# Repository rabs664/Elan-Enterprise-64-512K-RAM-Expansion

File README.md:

# Elan-Enterprise-64-512K-RAM-Expansion

>[!CAUTION]
>USE AT YOUR OWN RISK.
>There is always the risk that this 512k RAM Expansion could cause harm to your Enterprise. Although I have tested the 512K RAM Expansion, there is no guarantee that it will work properly under all circumstances.
>
>I am not an Enterprise Expert and still learning about this machine. What you see here is an intepretation of what I have found on the web, see the acknowledgements.

>[!WARNING]
>There is not a lot of room under the keyboard and the jumper wire connectors are a tight fit. There is probably a better solution to this.
>
> Also the EXP1 connector does not have standard spacing and you have to use two separate headers.
>
> 

## Project History
### 27 June 2026
First Releae

## Acknowledgements
- [Supid Humans Inc EP RAM](https://github.com/StupidHumansInc/EP_RAM)
- [Andra Santos](https://github.com/andrastantos/enterprise_mem_extender)

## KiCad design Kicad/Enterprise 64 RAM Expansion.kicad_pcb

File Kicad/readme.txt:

This folder contains the Kicad project files and gerbers.

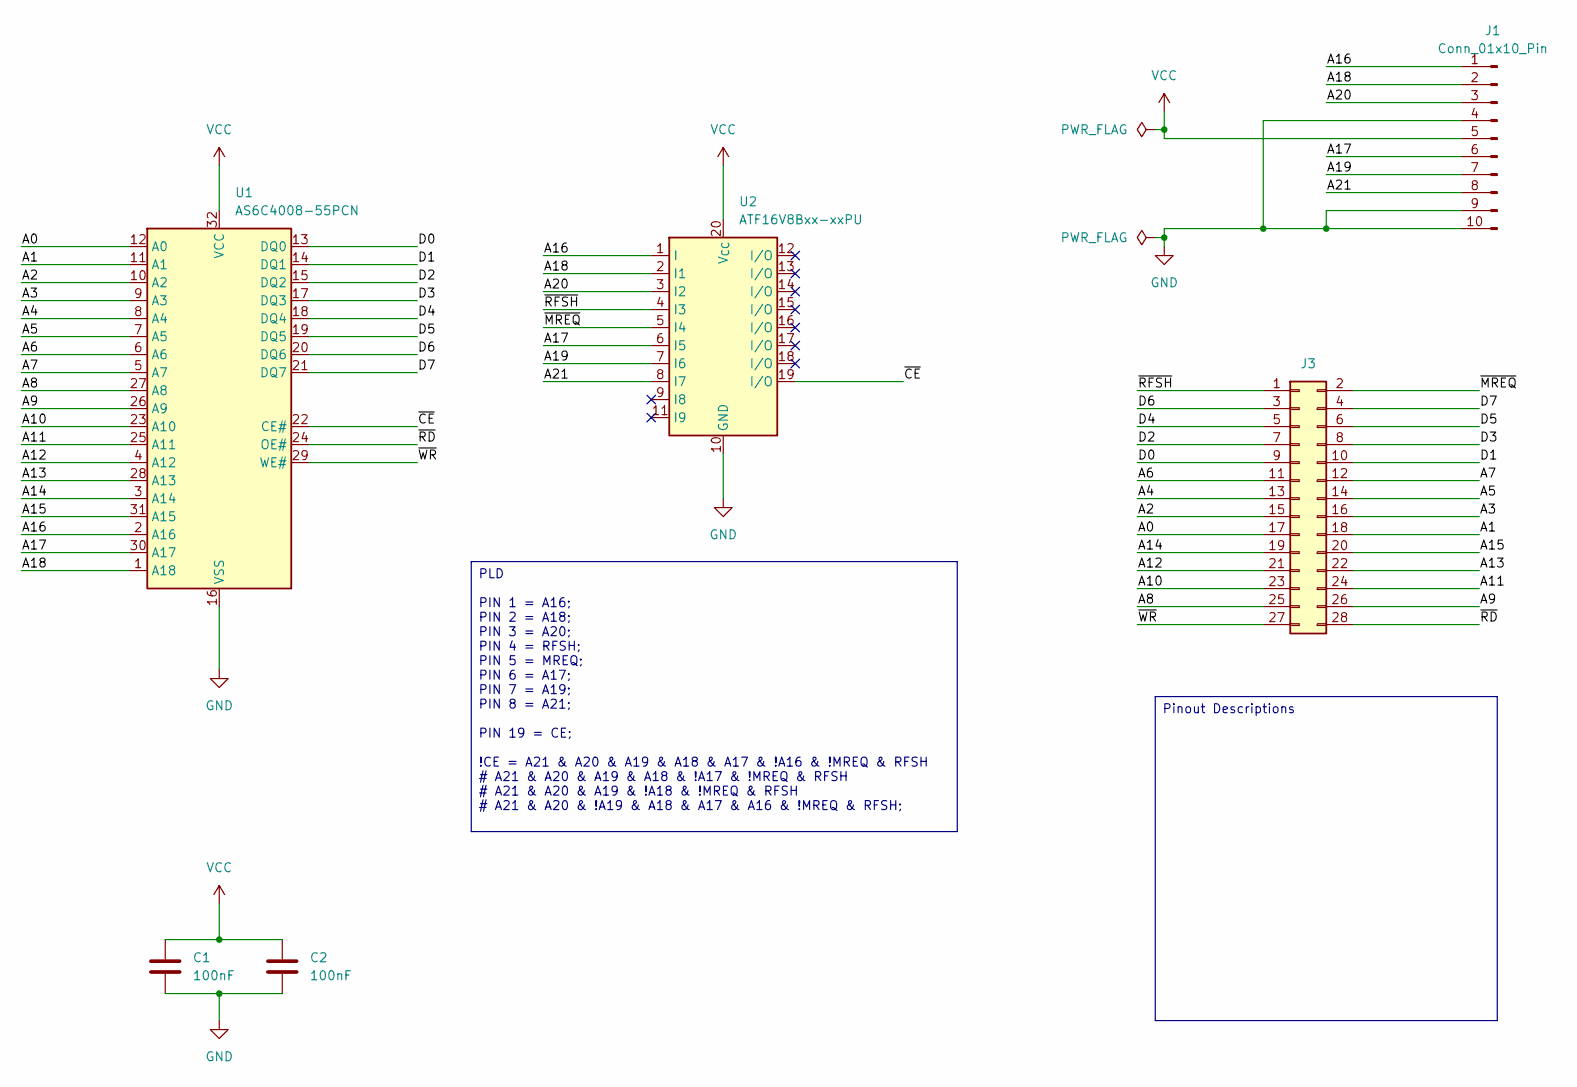
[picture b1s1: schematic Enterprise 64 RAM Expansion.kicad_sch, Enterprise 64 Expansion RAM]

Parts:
C1, C2: 100nF; C_0805_2012Metric_Pad1.18x1.45mm_HandSolder
J1: Conn_01x10_Pin; PinHeader_1x10_P2.54mm_Horizontal
J3: Conn_02x16_Row_Letter_First; PinSocket_2x14_P2.54mm_Vertical
U1: AS6C4008-55PCN; SOP-32_11.305x20.495mm_P1.27mm
U2: ATF16V8Bxx-xxPU; SOIC-20W_7.5x12.8mm_P1.27mm

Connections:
/A0: J3.17, U1.12 (A0)
/A1: J3.18, U1.11 (A1)
/A2: J3.15, U1.10 (A2)
/A3: J3.16, U1.9 (A3)
/A4: J3.13, U1.8 (A4)
/A5: J3.14, U1.7 (A5)
/A6: J3.11, U1.6 (A6)
/A7: J3.12, U1.5 (A7)
/A8: J3.25, U1.27 (A8)
/A9: J3.26, U1.26 (A9)
/A10: J3.23, U1.23 (A10)
/A11: J3.24, U1.25 (A11)
/A12: J3.21, U1.4 (A12)
/A13: J3.22, U1.28 (A13)
/A14: J3.19, U1.3 (A14)
/A15: J3.20, U1.31 (A15)
/A16: J1.1, U1.2 (A16), U2.1 (I)
/A17: J1.6, U1.30 (A17), U2.6 (I5)
/A18: J1.2, U1.1 (A18), U2.2 (I1)
/A19: J1.7, U2.7 (I6)
/A20: J1.3, U2.3 (I2)
/A21: J1.8, U2.8 (I7)
/D0: J3.9, U1.13 (DQ0)
/D1: J3.10, U1.14 (DQ1)
/D2: J3.7, U1.15 (DQ2)
/D3: J3.8, U1.17 (DQ3)
/D4: J3.5, U1.18 (DQ4)
/D5: J3.6, U1.19 (DQ5)
/D6: J3.3, U1.20 (DQ6)
/D7: J3.4, U1.21 (DQ7)
/~CE: U1.22 (CE#), U2.19 (I/O)
/~MREQ: J3.2, U2.5 (I4)
/~RD: J3.28, U1.24 (OE#)
/~RFSH: J3.1, U2.4 (I3)
/~WR: J3.27, U1.29 (WE#)
GND: C1.2, C2.2, J1.4, J1.9, J1.10, U1.16 (VSS), U2.10 (GND)
VCC: C1.1, C2.1, J1.5, U1.32 (VCC), U2.20 (V_{CC})

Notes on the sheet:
Pinout Descriptions
PLD PIN 1 = A16; PIN 2 = A18; PIN 3 = A20; PIN 4 = RFSH; PIN 5 = MREQ; PIN 6 = A17; PIN 7 = A19; PIN 8 = A21; PIN 19 = CE; !CE = A21 & A20 & A19 & A18 & A17 & !A16 & !MREQ & RFSH # A21 & A20 & A19 & A18 & !A17 & !MREQ & RFSH # A21 & A20 & A19 & !A18 & !MREQ & RFSH # A21 & A20 & !A19 & A18 & A17 & A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

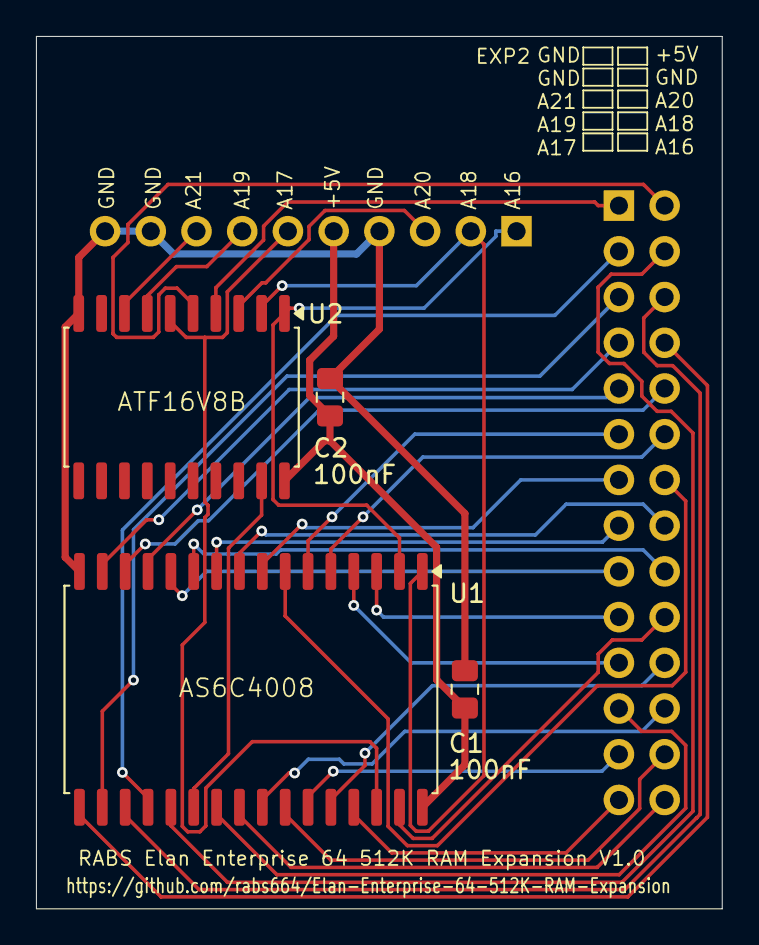
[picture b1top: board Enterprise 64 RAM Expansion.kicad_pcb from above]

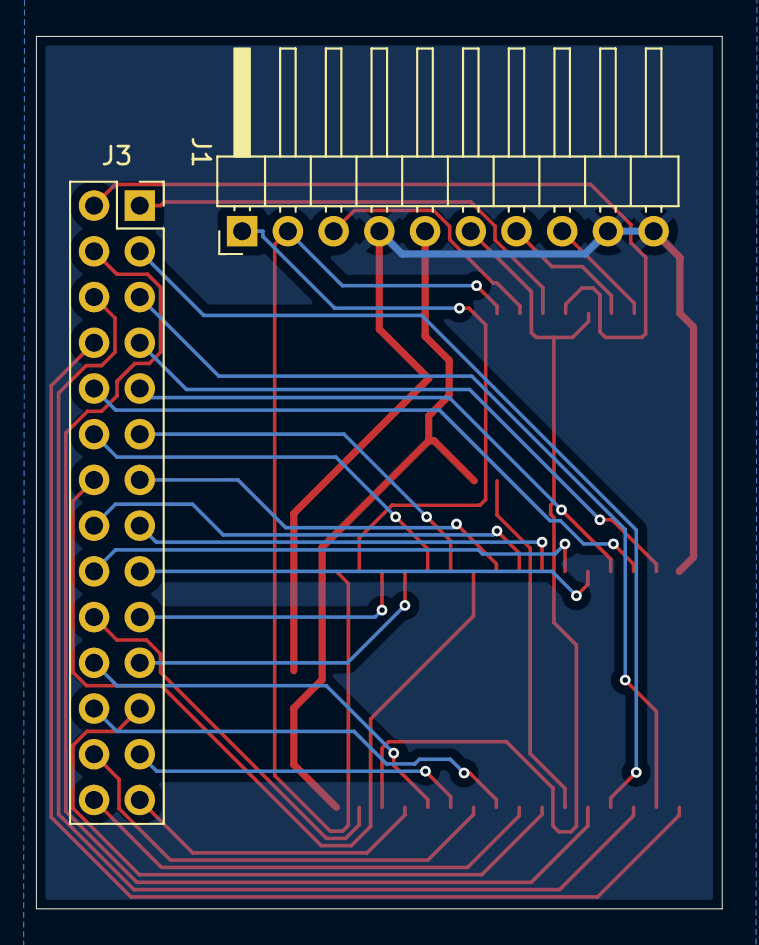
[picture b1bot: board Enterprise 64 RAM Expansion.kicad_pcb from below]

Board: 2 copper layers, 38.1 x 48.5 mm, 6 parts (2 on the bottom side), 37 nets.

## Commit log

2026-06-26 Create PLD
2026-06-26 Add readme.txt for PLD logic documentation
2026-06-27 Update README with project details and warnings
2026-06-27 Add readme for Kicad project files
